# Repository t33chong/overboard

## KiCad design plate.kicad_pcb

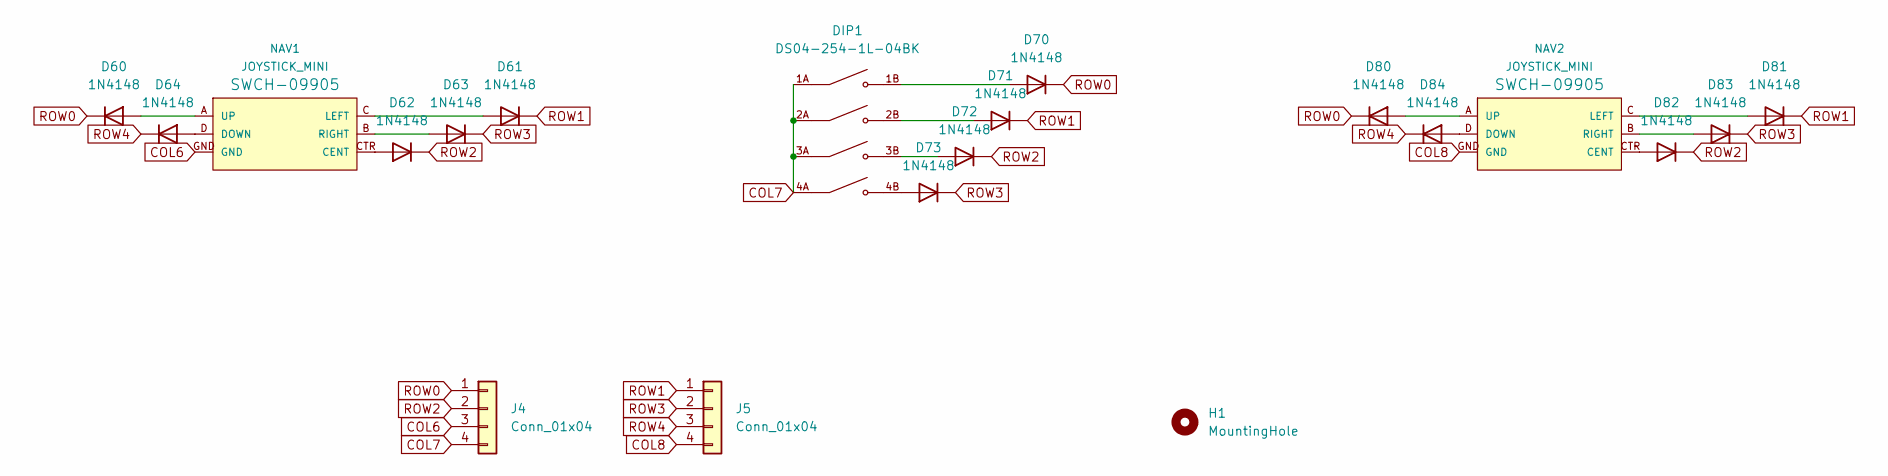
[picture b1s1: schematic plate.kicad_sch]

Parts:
D60, D61, D62, D63, D64, D70, D71, D72, D73, D80, D81, D82, D83, D84: 1N4148; D_SOD-123
DIP1: DS04-254-1L-04BK; PARTREV V0.0
H1: MountingHole; Trackpoint_Mounting_Holes
J4, J5: Conn_01x04; PinHeader_1x04_P2.54mm_Vertical_SMD_Pin1Right
NAV1, NAV2: JOYSTICK_MINI

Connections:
COL6: J4.3, NAV1.GND
COL7: DIP1.1A, DIP1.2A, DIP1.3A, DIP1.4A, J4.4
COL8: J5.4, NAV2.GND
unnamed: D60.2 (A), NAV1.A (UP)
unnamed: D61.2 (A), NAV1.C (LEFT)
unnamed: D62.2 (A), NAV1.CTR (CENT)
unnamed: D63.2 (A), NAV1.B (RIGHT)
unnamed: D64.2 (A), NAV1.D (DOWN)
unnamed: D70.2 (A), DIP1.1B
unnamed: D71.2 (A), DIP1.2B
unnamed: D72.2 (A), DIP1.3B
unnamed: D73.2 (A), DIP1.4B
unnamed: D80.2 (A), NAV2.A (UP)
unnamed: D81.2 (A), NAV2.C (LEFT)
unnamed: D82.2 (A), NAV2.CTR (CENT)
unnamed: D83.2 (A), NAV2.B (RIGHT)
unnamed: D84.2 (A), NAV2.D (DOWN)
ROW0: D60.1 (K), D70.1 (K), D80.1 (K), J4.1
ROW1: D61.1 (K), D71.1 (K), D81.1 (K), J5.1
ROW2: D62.1 (K), D72.1 (K), D82.1 (K), J4.2
ROW3: D63.1 (K), D73.1 (K), D83.1 (K), J5.2
ROW4: D64.1 (K), D84.1 (K), J5.3

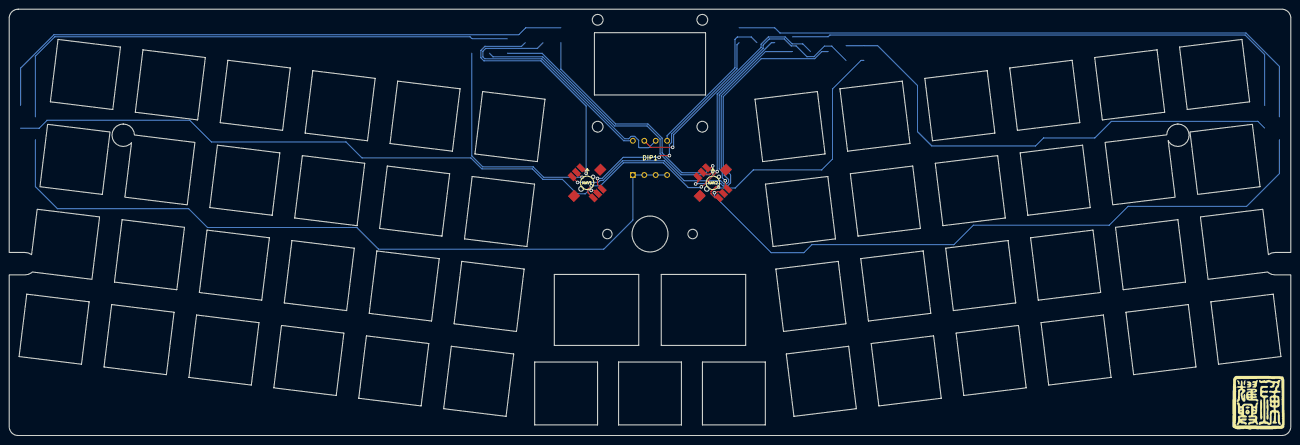
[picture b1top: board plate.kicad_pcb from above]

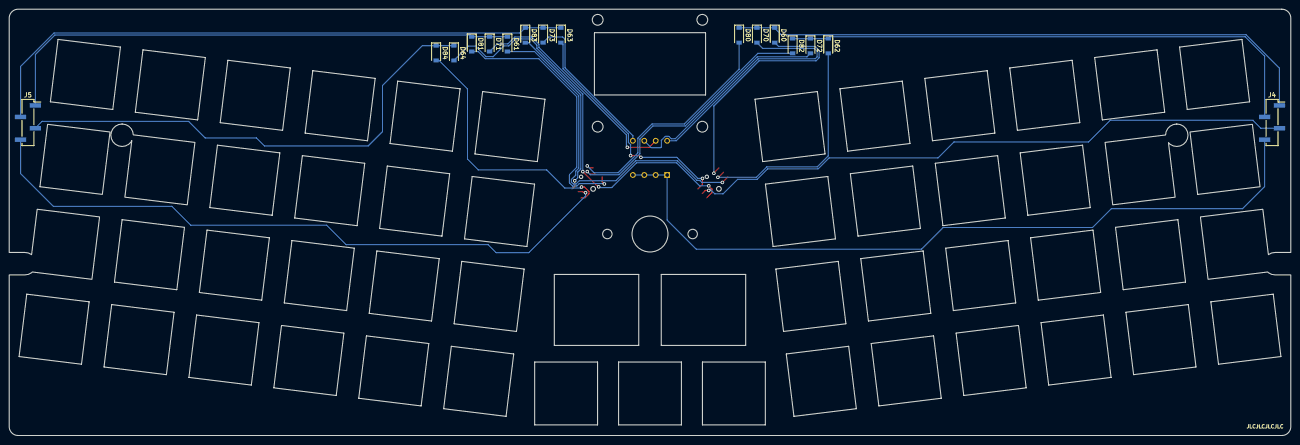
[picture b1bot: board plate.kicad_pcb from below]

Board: 2 copper layers, 285.3 x 94.9 mm, 70 parts (17 on the bottom side), 22 nets.

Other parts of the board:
ENC1, ENC2: Panasonic_EVQ-WGD001_Plate_Edge_Cuts
K00, K03, K10, K12, K13, K20, K21, K22, K23, K30, K31, K32, K33, K40, K41, K42, K43, K50, K51, K52, K53, K92, K93, K94: MX_cutout
KA0, KA1, KA2, KA3: MX_cutout
KB0, KB1, KB2, KB3: MX_cutout
KC0, KC1, KC2, KC3: MX_cutout
KD0, KD1, KD2, KD3: MX_cutout
KE0, KE2, KE3: MX_cutout
KF0, KF3: MX_cutout
OLED1: 128x64OLED_Edge_Cuts
Ref**: Val**; Seal_Logo_12mm
svg2mod: G***; Overboard_Plate

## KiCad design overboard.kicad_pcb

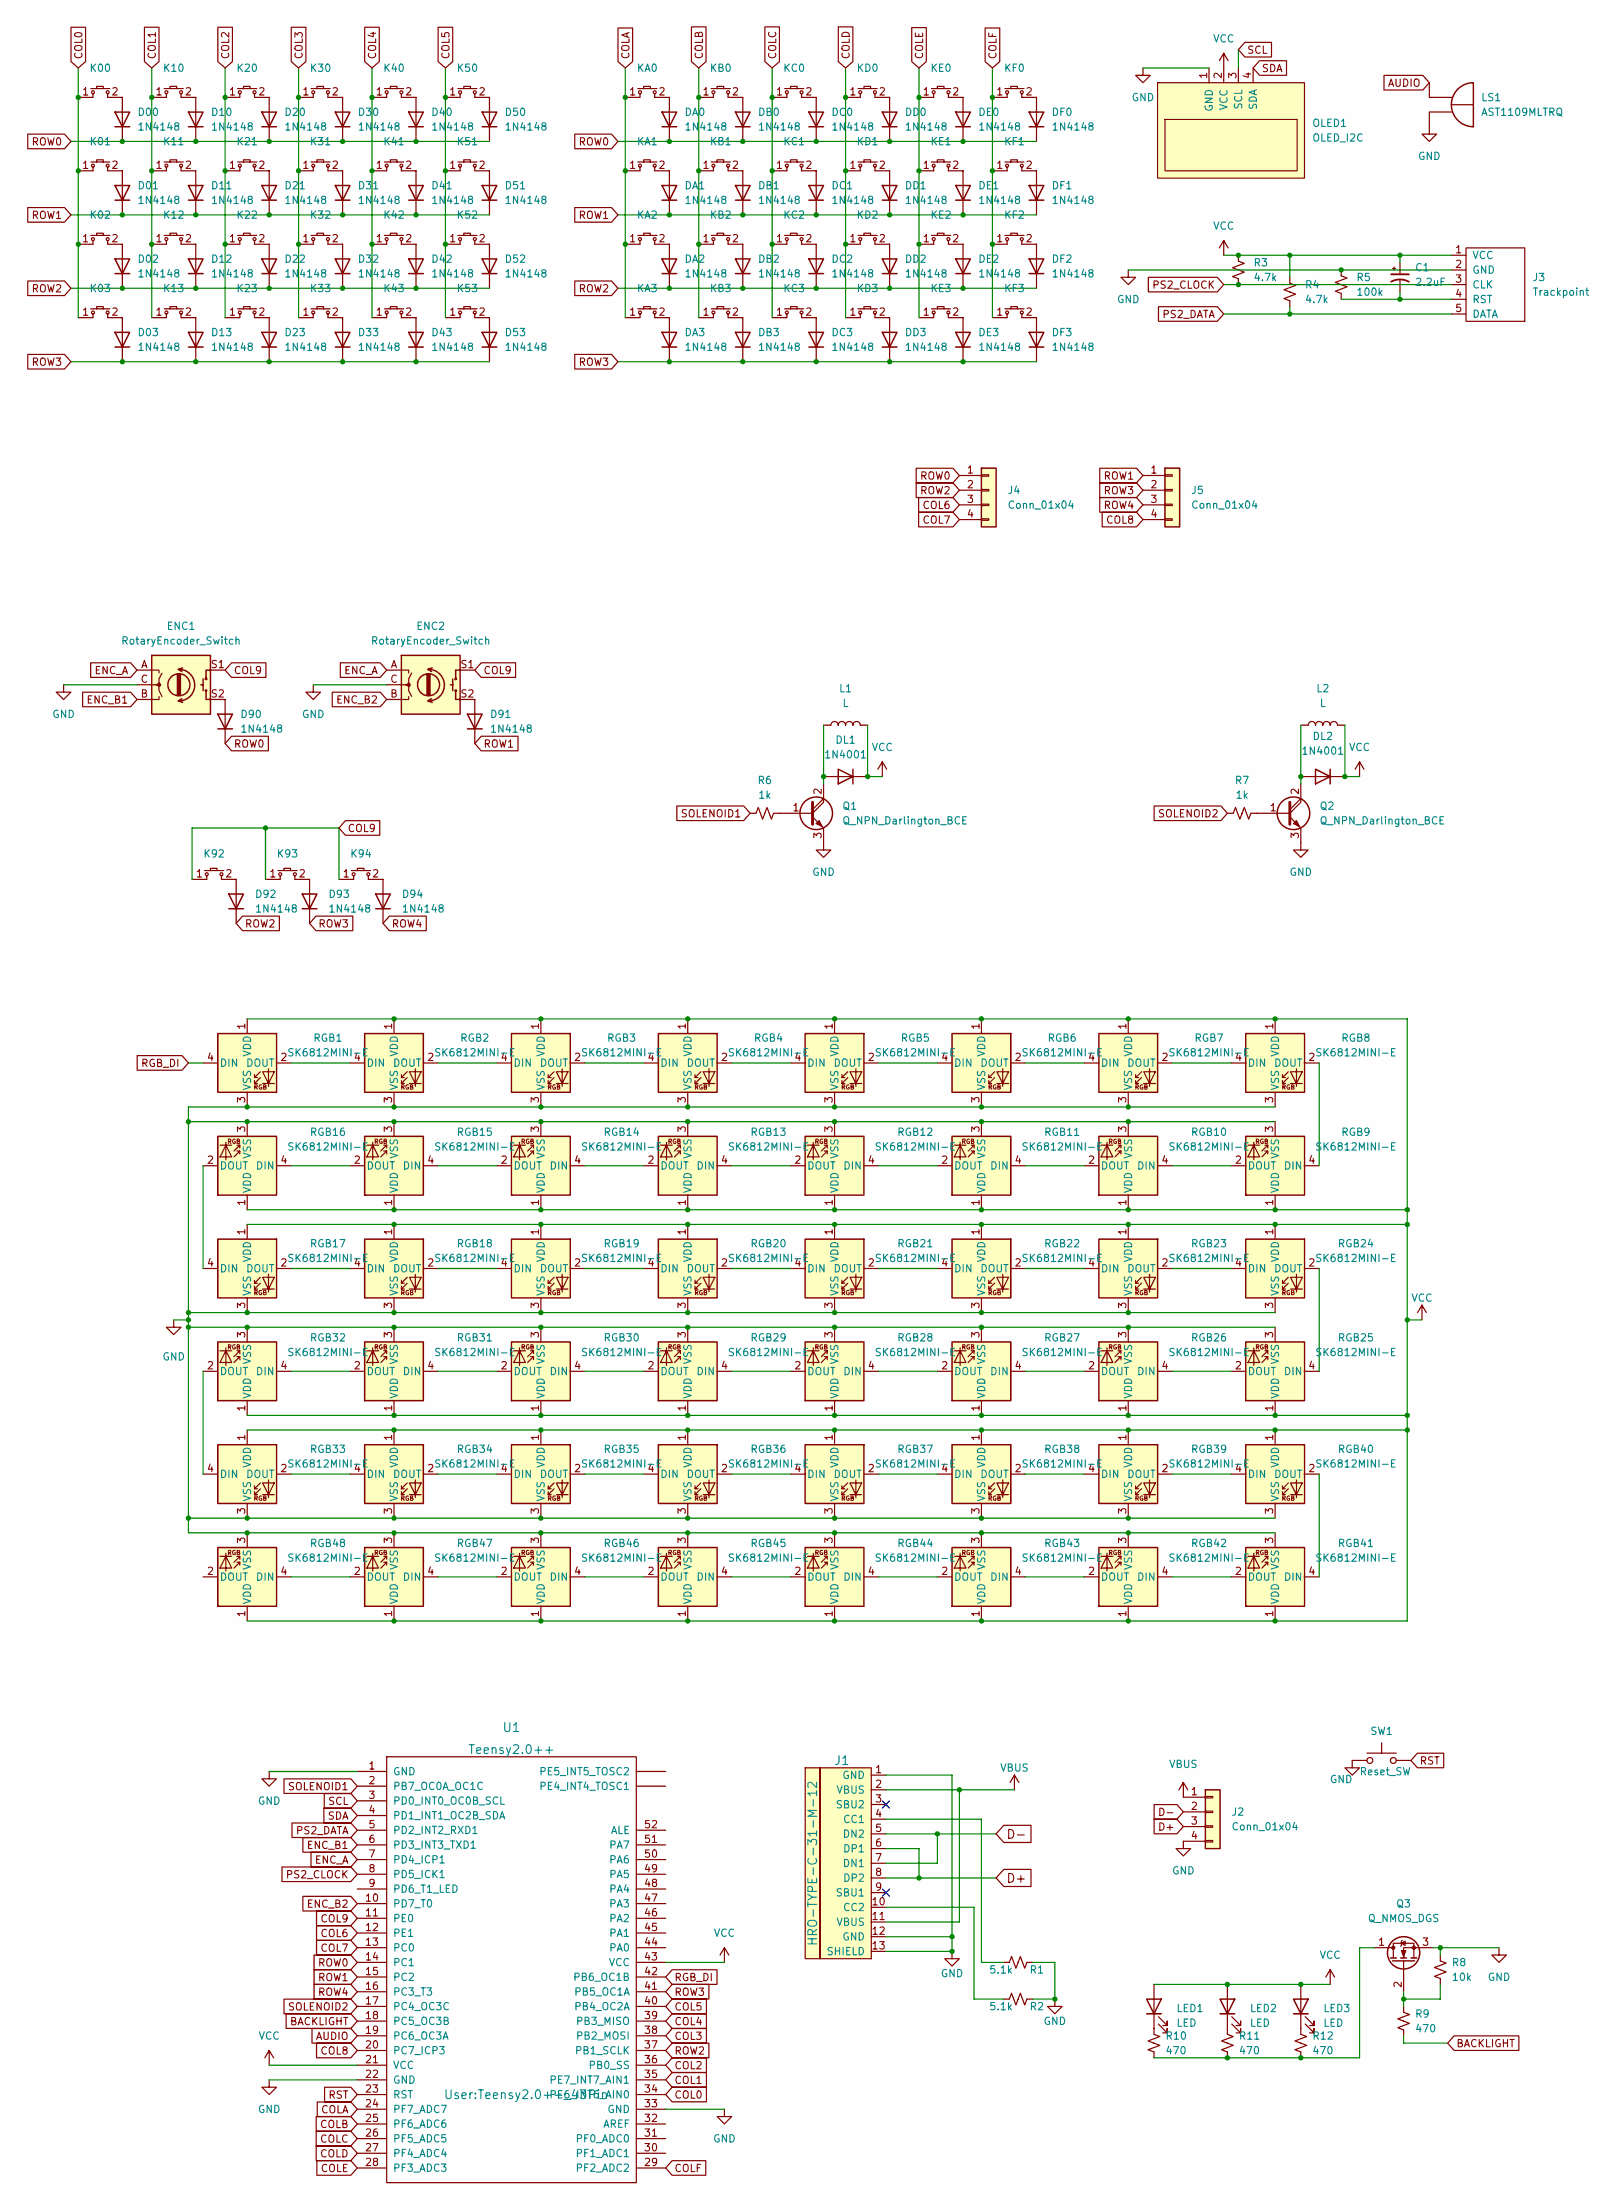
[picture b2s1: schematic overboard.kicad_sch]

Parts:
C1: 2.2uF; C_Radial_D4.0mm_H7.0mm_P1.50mm
D00, D01, D02, D03, D10, D11, D12, D13, D20, D21, D22, D23, D30, D31, D32, D33, D40, D41, D42, D43, D50, D51, D52, D53, D90, D91, D92, D93, D94: 1N4148; Diode_THT_P7.62mm
DA0, DA1, DA2, DA3: 1N4148; Diode_THT_P7.62mm
DB0, DB1, DB2, DB3: 1N4148; Diode_THT_P7.62mm
DC0, DC1, DC2, DC3: 1N4148; Diode_THT_P7.62mm
DD0, DD1, DD2, DD3: 1N4148; Diode_THT_P7.62mm
DE0, DE1, DE2, DE3: 1N4148; Diode_THT_P7.62mm
DF0, DF1, DF2, DF3: 1N4148; Diode_THT_P7.62mm
DL1, DL2: 1N4001
ENC1, ENC2: RotaryEncoder_Switch; Panasonic_EVQ-WGD001_LargerCutout
J1: HRO-TYPE-C-31-M-12; HRO-TYPE-C-31-M-12-HandSoldering
J2: Conn_01x04; PinHeader_1x04_P2.54mm_Horizontal
J3: Trackpoint; PinHeader_1x05_P2.54mm_Horizontal
J4, J5: Conn_01x04; PinHeader_1x04_P2.54mm_Vertical_Centered
K00, K01, K02, K03, K10, K11, K12, K13, K20, K21, K22, K23, K30, K31, K32, K33, K40, K41, K42, K43, K50, K51, K52, K53, K92, K93, K94: Key_Switch; MXOnly-1U
KA0, KA1, KA2, KA3: Key_Switch; MXOnly-1U
KB0, KB1, KB2, KB3: Key_Switch; MXOnly-1U
KC0, KC1, KC2, KC3: Key_Switch; MXOnly-1U
KD0, KD1, KD2, KD3: Key_Switch; MXOnly-1U
KE0, KE1, KE2, KE3: Key_Switch; MXOnly-1U
KF0, KF1, KF2, KF3: Key_Switch; MXOnly-1U
L1, L2: L; JST_PH_S2B-PH-K_1x02_P2.00mm_Horizontal
LED1, LED2, LED3: LED; LED_D1.8mm_W3.3mm_H2.4mm
LS1: AST1109MLTRQ; Buzzer_Mallory_AST1109MLTRQ; PARTREV B
OLED1: OLED_I2C; 128x64OLED
Q1, Q2: Q_NPN_Darlington_BCE; TO-220-3
Q3: Q_NMOS_DGS; TO-220-3
R1, R2: 5.1k; Resistor_THT_P7.62mm
R3, R4: 4.7k; Resistor_THT_P7.62mm
R5: 100k; Resistor_THT_P7.62mm
R6, R7: 1k; Resistor_THT_P7.62mm
R8: 10k; Resistor_THT_P7.62mm
R9, R10, R11, R12: 470; Resistor_THT_P7.62mm
RGB1, RGB2, RGB3, RGB4, RGB5, RGB6, RGB7, RGB8, RGB9, RGB10, RGB11, RGB12, RGB13, RGB14, RGB15, RGB16, RGB17, RGB18, RGB19, RGB20, RGB21, RGB22, RGB23, RGB24, RGB25, RGB26, RGB27, RGB28, RGB29, RGB30, RGB31, RGB32, RGB33, RGB34, RGB35, RGB36, RGB37, RGB38, RGB39, RGB40, RGB41, RGB42, RGB43, RGB44, RGB45, RGB46, RGB47, RGB48: SK6812MINI-E; SK6812MINI-E_RGB_LED_3.2x2.8mm
SW1: Reset_SW; Panasonic_EVPAW
U1: Teensy2.0++; Teensy2.0++_43Pin

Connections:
AUDIO: LS1.1, U1.19 (PC6_OC3A)
BACKLIGHT: R9.2, U1.18 (PC5_OC3B)
COL0: K00.1, K01.1, K02.1, K03.1, U1.34 (PE6_INT6_AIN0)
COL1: K10.1, K11.1, K12.1, K13.1, U1.35 (PE7_INT7_AIN1)
COL2: K20.1, K21.1, K22.1, K23.1, U1.36 (PB0_SS)
COL3: K30.1, K31.1, K32.1, K33.1, U1.38 (PB2_MOSI)
COL4: K40.1, K41.1, K42.1, K43.1, U1.39 (PB3_MISO)
COL5: K50.1, K51.1, K52.1, K53.1, U1.40 (PB4_OC2A)
COL6: J4.3, U1.12 (PE1)
COL7: J4.4, U1.13 (PC0)
COL8: J5.4, U1.20 (PC7_ICP3)
COL9: ENC1.S1, ENC2.S1, K92.1, K93.1, K94.1, U1.11 (PE0)
COLA: KA0.1, KA1.1, KA2.1, KA3.1, U1.24 (PF7_ADC7)
COLB: KB0.1, KB1.1, KB2.1, KB3.1, U1.25 (PF6_ADC6)
COLC: KC0.1, KC1.1, KC2.1, KC3.1, U1.26 (PF5_ADC5)
COLD: KD0.1, KD1.1, KD2.1, KD3.1, U1.27 (PF4_ADC4)
COLE: KE0.1, KE1.1, KE2.1, KE3.1, U1.28 (PF3_ADC3)
COLF: KF0.1, KF1.1, KF2.1, KF3.1, U1.29 (PF2_ADC2)
D+: J1.6 (DP1), J1.8 (DP2), J2.3
D-: J1.5 (DN2), J1.7 (DN1), J2.2
ENC_A: ENC1.A, ENC2.A, U1.7 (PD4_ICP1)
ENC_B1: ENC1.B, U1.6 (PD3_INT3_TXD1)
ENC_B2: ENC2.B, U1.10 (PD7_T0)
GND: ENC1.C, ENC2.C, J1.1 (GND), J1.12 (GND), J1.13 (SHIELD), J2.4, J3.2 (GND), LS1.2, OLED1.1 (GND), Q1.3 (E), Q2.3 (E), Q3.3 (S), R1.1, R2.1, R5.1, R8.1, RGB1.3 (VSS), RGB2.3 (VSS), RGB3.3 (VSS), RGB4.3 (VSS), RGB5.3 (VSS), RGB6.3 (VSS), RGB7.3 (VSS), RGB8.3 (VSS), RGB9.3 (VSS), RGB10.3 (VSS), RGB11.3 (VSS), RGB12.3 (VSS), RGB13.3 (VSS), RGB14.3 (VSS), RGB15.3 (VSS), RGB16.3 (VSS), RGB17.3 (VSS), RGB18.3 (VSS), RGB19.3 (VSS), RGB20.3 (VSS), RGB21.3 (VSS), RGB22.3 (VSS), RGB23.3 (VSS), RGB24.3 (VSS), RGB25.3 (VSS), RGB26.3 (VSS), RGB27.3 (VSS), RGB28.3 (VSS), RGB29.3 (VSS), RGB30.3 (VSS), RGB31.3 (VSS), RGB32.3 (VSS), RGB33.3 (VSS), RGB34.3 (VSS), RGB35.3 (VSS), RGB36.3 (VSS), RGB37.3 (VSS), RGB38.3 (VSS), RGB39.3 (VSS), RGB40.3 (VSS), RGB41.3 (VSS), RGB42.3 (VSS), RGB43.3 (VSS), RGB44.3 (VSS), RGB45.3 (VSS), RGB46.3 (VSS), RGB47.3 (VSS), RGB48.3 (VSS), SW1.1, U1.1 (GND), U1.22 (GND), U1.33 (GND)
unnamed: C1.2, J3.4 (RST), R5.2
unnamed: D00.2 (A), K00.2
unnamed: D01.2 (A), K01.2
unnamed: D02.2 (A), K02.2
unnamed: D03.2 (A), K03.2
unnamed: D10.2 (A), K10.2
unnamed: D11.2 (A), K11.2
unnamed: D12.2 (A), K12.2
unnamed: D13.2 (A), K13.2
unnamed: D20.2 (A), K20.2
unnamed: D21.2 (A), K21.2
unnamed: D22.2 (A), K22.2
unnamed: D23.2 (A), K23.2
unnamed: D30.2 (A), K30.2
unnamed: D31.2 (A), K31.2
unnamed: D32.2 (A), K32.2
unnamed: D33.2 (A), K33.2
unnamed: D40.2 (A), K40.2
unnamed: D41.2 (A), K41.2
unnamed: D42.2 (A), K42.2
unnamed: D43.2 (A), K43.2
unnamed: D50.2 (A), K50.2
unnamed: D51.2 (A), K51.2
unnamed: D52.2 (A), K52.2
unnamed: D53.2 (A), K53.2
unnamed: D90.2 (A), ENC1.S2
unnamed: D91.2 (A), ENC2.S2
unnamed: D92.2 (A), K92.2
unnamed: D93.2 (A), K93.2
unnamed: D94.2 (A), K94.2
unnamed: DA0.2 (A), KA0.2
unnamed: DA1.2 (A), KA1.2
unnamed: DA2.2 (A), KA2.2
unnamed: DA3.2 (A), KA3.2
unnamed: DB0.2 (A), KB0.2
unnamed: DB1.2 (A), KB1.2
unnamed: DB2.2 (A), KB2.2
unnamed: DB3.2 (A), KB3.2
unnamed: DC0.2 (A), KC0.2
unnamed: DC1.2 (A), KC1.2
unnamed: DC2.2 (A), KC2.2
unnamed: DC3.2 (A), KC3.2
unnamed: DD0.2 (A), KD0.2
unnamed: DD1.2 (A), KD1.2
unnamed: DD2.2 (A), KD2.2
unnamed: DD3.2 (A), KD3.2
unnamed: DE0.2 (A), KE0.2
unnamed: DE1.2 (A), KE1.2
unnamed: DE2.2 (A), KE2.2
unnamed: DE3.2 (A), KE3.2
unnamed: DF0.2 (A), KF0.2
unnamed: DF1.2 (A), KF1.2
unnamed: DF2.2 (A), KF2.2
unnamed: DF3.2 (A), KF3.2
unnamed: DL1.2 (A), L1.1, Q1.2 (C)
unnamed: DL2.2 (A), L2.1, Q2.2 (C)
unnamed: J1.4 (CC1), R1.2
unnamed: J1.10 (CC2), R2.2
unnamed: LED1.1 (K), R10.1
unnamed: LED2.1 (K), R11.1
unnamed: LED3.1 (K), R12.1
unnamed: Q1.1 (B), R6.2
unnamed: Q2.1 (B), R7.2
unnamed: Q3.1 (D), R10.2, R11.2, R12.2
unnamed: Q3.2 (G), R8.2, R9.1
unnamed: RGB1.2 (DOUT), RGB2.4 (DIN)
unnamed: RGB2.2 (DOUT), RGB3.4 (DIN)
unnamed: RGB3.2 (DOUT), RGB4.4 (DIN)
unnamed: RGB4.2 (DOUT), RGB5.4 (DIN)
unnamed: RGB5.2 (DOUT), RGB6.4 (DIN)
unnamed: RGB6.2 (DOUT), RGB7.4 (DIN)
unnamed: RGB7.2 (DOUT), RGB8.4 (DIN)
unnamed: RGB8.2 (DOUT), RGB9.4 (DIN)
unnamed: RGB10.2 (DOUT), RGB11.4 (DIN)
unnamed: RGB9.2 (DOUT), RGB10.4 (DIN)
unnamed: RGB11.2 (DOUT), RGB12.4 (DIN)
unnamed: RGB12.2 (DOUT), RGB13.4 (DIN)
unnamed: RGB13.2 (DOUT), RGB14.4 (DIN)
unnamed: RGB14.2 (DOUT), RGB15.4 (DIN)
unnamed: RGB15.2 (DOUT), RGB16.4 (DIN)
unnamed: RGB16.2 (DOUT), RGB17.4 (DIN)
unnamed: RGB17.2 (DOUT), RGB18.4 (DIN)
unnamed: RGB18.2 (DOUT), RGB19.4 (DIN)
unnamed: RGB19.2 (DOUT), RGB20.4 (DIN)
unnamed: RGB20.2 (DOUT), RGB21.4 (DIN)
unnamed: RGB21.2 (DOUT), RGB22.4 (DIN)
unnamed: RGB22.2 (DOUT), RGB23.4 (DIN)
unnamed: RGB23.2 (DOUT), RGB24.4 (DIN)
unnamed: RGB24.2 (DOUT), RGB25.4 (DIN)
unnamed: RGB25.2 (DOUT), RGB26.4 (DIN)
unnamed: RGB26.2 (DOUT), RGB27.4 (DIN)
unnamed: RGB27.2 (DOUT), RGB28.4 (DIN)
unnamed: RGB28.2 (DOUT), RGB29.4 (DIN)
unnamed: RGB29.2 (DOUT), RGB30.4 (DIN)
unnamed: RGB30.2 (DOUT), RGB31.4 (DIN)
unnamed: RGB31.2 (DOUT), RGB32.4 (DIN)
unnamed: RGB32.2 (DOUT), RGB33.4 (DIN)
unnamed: RGB33.2 (DOUT), RGB34.4 (DIN)
unnamed: RGB34.2 (DOUT), RGB35.4 (DIN)
unnamed: RGB35.2 (DOUT), RGB36.4 (DIN)
unnamed: RGB36.2 (DOUT), RGB37.4 (DIN)
unnamed: RGB37.2 (DOUT), RGB38.4 (DIN)
unnamed: RGB38.2 (DOUT), RGB39.4 (DIN)
unnamed: RGB39.2 (DOUT), RGB40.4 (DIN)
unnamed: RGB40.2 (DOUT), RGB41.4 (DIN)
unnamed: RGB41.2 (DOUT), RGB42.4 (DIN)
unnamed: RGB42.2 (DOUT), RGB43.4 (DIN)
unnamed: RGB43.2 (DOUT), RGB44.4 (DIN)
unnamed: RGB44.2 (DOUT), RGB45.4 (DIN)
unnamed: RGB45.2 (DOUT), RGB46.4 (DIN)
unnamed: RGB46.2 (DOUT), RGB47.4 (DIN)
unnamed: RGB47.2 (DOUT), RGB48.4 (DIN)
PS2_CLOCK: J3.3 (CLK), R3.2, U1.8 (PD5_ICK1)
PS2_DATA: J3.5 (DATA), R4.2, U1.5 (PD2_INT2_RXD1)
RGB_DI: RGB1.4 (DIN), U1.42 (PB6_OC1B)
ROW0: D00.1 (K), D10.1 (K), D20.1 (K), D30.1 (K), D40.1 (K), D50.1 (K), D90.1 (K), DA0.1 (K), DB0.1 (K), DC0.1 (K), DD0.1 (K), DE0.1 (K), DF0.1 (K), J4.1, U1.14 (PC1)
ROW1: D01.1 (K), D11.1 (K), D21.1 (K), D31.1 (K), D41.1 (K), D51.1 (K), D91.1 (K), DA1.1 (K), DB1.1 (K), DC1.1 (K), DD1.1 (K), DE1.1 (K), DF1.1 (K), J5.1, U1.15 (PC2)
ROW2: D02.1 (K), D12.1 (K), D22.1 (K), D32.1 (K), D42.1 (K), D52.1 (K), D92.1 (K), DA2.1 (K), DB2.1 (K), DC2.1 (K), DD2.1 (K), DE2.1 (K), DF2.1 (K), J4.2, U1.37 (PB1_SCLK)
ROW3: D03.1 (K), D13.1 (K), D23.1 (K), D33.1 (K), D43.1 (K), D53.1 (K), D93.1 (K), DA3.1 (K), DB3.1 (K), DC3.1 (K), DD3.1 (K), DE3.1 (K), DF3.1 (K), J5.2, U1.41 (PB5_OC1A)
ROW4: D94.1 (K), J5.3, U1.16 (PC3_T3)
RST: SW1.2, U1.23 (RST)
SCL: OLED1.3 (SCL), U1.3 (PD0_INT0_OC0B_SCL)
SDA: OLED1.4 (SDA), U1.4 (PD1_INT1_OC2B_SDA)
SOLENOID1: R6.1, U1.2 (PB7_OC0A_OC1C)
SOLENOID2: R7.1, U1.17 (PC4_OC3C)
VBUS: J1.2 (VBUS), J1.11 (VBUS), J2.1
VCC: C1.1, DL1.1 (K), DL2.1 (K), J3.1 (VCC), L1.2, L2.2, LED1.2 (A), LED2.2 (A), LED3.2 (A), OLED1.2 (VCC), R3.1, R4.1, RGB1.1 (VDD), RGB2.1 (VDD), RGB3.1 (VDD), RGB4.1 (VDD), RGB5.1 (VDD), RGB6.1 (VDD), RGB7.1 (VDD), RGB8.1 (VDD), RGB9.1 (VDD), RGB10.1 (VDD), RGB11.1 (VDD), RGB12.1 (VDD), RGB13.1 (VDD), RGB14.1 (VDD), RGB15.1 (VDD), RGB16.1 (VDD), RGB17.1 (VDD), RGB18.1 (VDD), RGB19.1 (VDD), RGB20.1 (VDD), RGB21.1 (VDD), RGB22.1 (VDD), RGB23.1 (VDD), RGB24.1 (VDD), RGB25.1 (VDD), RGB26.1 (VDD), RGB27.1 (VDD), RGB28.1 (VDD), RGB29.1 (VDD), RGB30.1 (VDD), RGB31.1 (VDD), RGB32.1 (VDD), RGB33.1 (VDD), RGB34.1 (VDD), RGB35.1 (VDD), RGB36.1 (VDD), RGB37.1 (VDD), RGB38.1 (VDD), RGB39.1 (VDD), RGB40.1 (VDD), RGB41.1 (VDD), RGB42.1 (VDD), RGB43.1 (VDD), RGB44.1 (VDD), RGB45.1 (VDD), RGB46.1 (VDD), RGB47.1 (VDD), RGB48.1 (VDD), U1.21 (VCC), U1.43 (VCC)

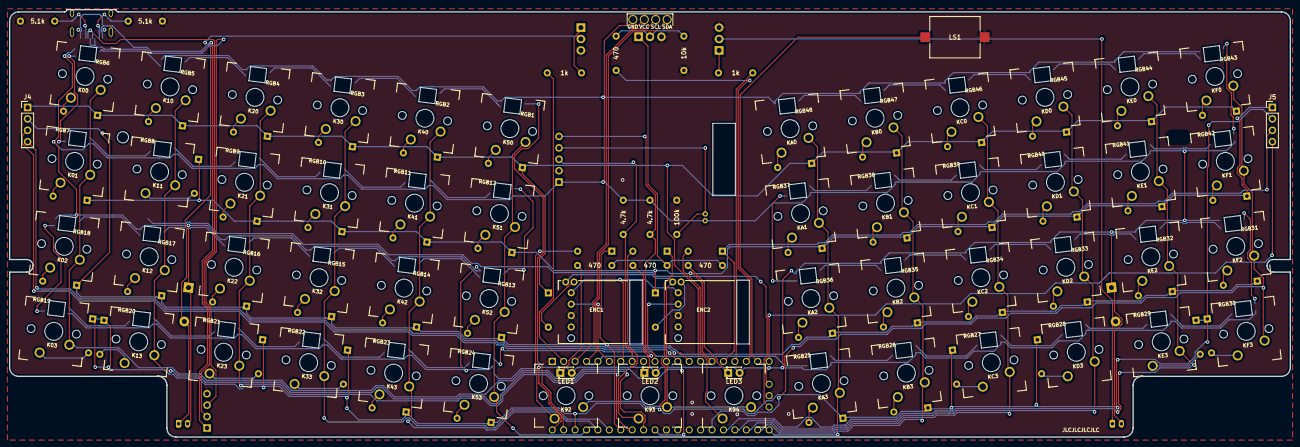
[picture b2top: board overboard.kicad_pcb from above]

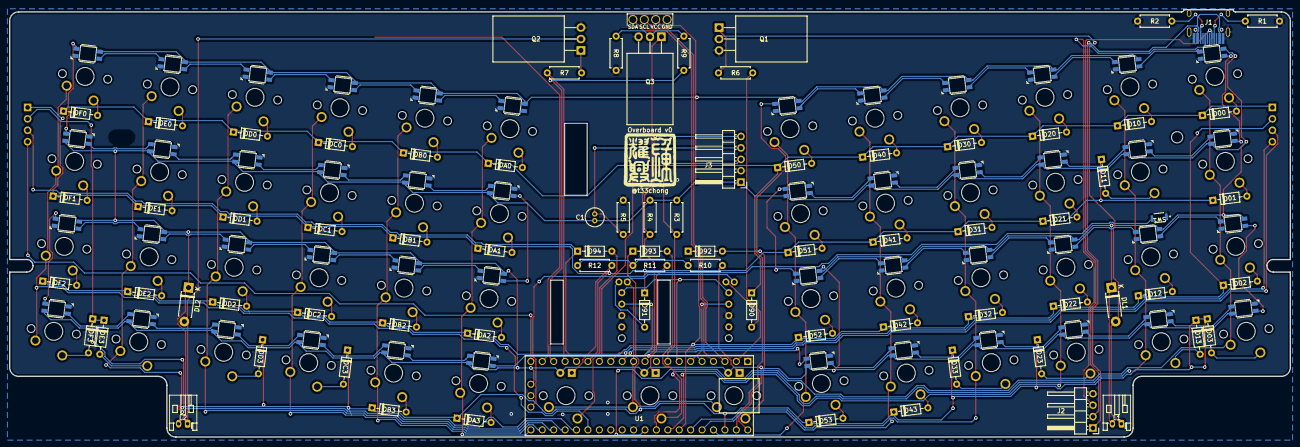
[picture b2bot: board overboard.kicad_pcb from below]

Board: 2 copper layers, 285.0 x 95.1 mm, 188 parts (126 on the bottom side), 151 nets.

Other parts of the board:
H1: G***; Trackpoint_Outline
Ref**: Val**; Seal_Logo_12mm

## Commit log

2022-06-16 Add USB-C port
2022-06-18 48 switch layout
2022-06-19 Add plate, place RGB LEDs
2022-06-19 Place diodes
2022-06-25 Place components
2022-07-01 Route PCB & plate
2022-07-01 Combine edge cuts for plate cutouts & switch holes
2022-07-01 Before deleting unaffected switch holes
